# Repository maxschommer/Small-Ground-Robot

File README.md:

# Small-Ground-Robot
A small, autonomous ground vehicle.

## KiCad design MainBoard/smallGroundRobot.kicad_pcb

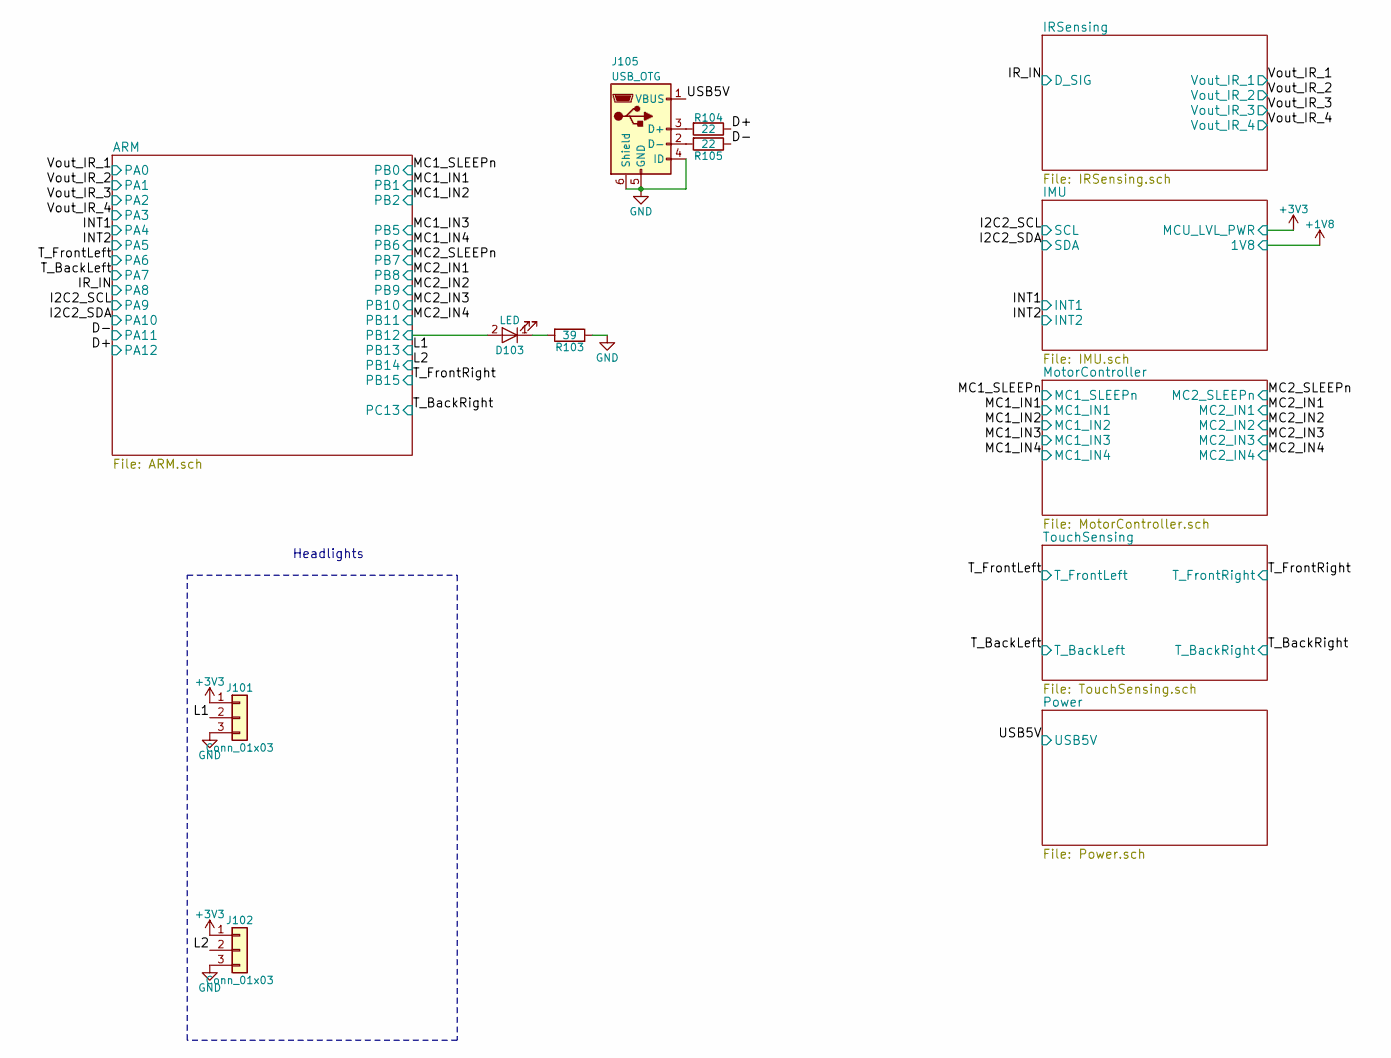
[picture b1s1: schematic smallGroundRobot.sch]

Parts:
D103: LED; LED_0805
J101, J102: Conn_01x03; Pin_Header_Angled_1x03_Pitch2.54mm
J105: USB_OTG; USB_Micro-B
R103: 39; R_0402
R104, R105: 22; R_0402

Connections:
+3V3: J101.1, J102.1; also elsewhere on the board
/ARM/PB12: D103.2 (A); also elsewhere on the board
/D+: R104.1; also elsewhere on the board
/D-: R105.1; also elsewhere on the board
/L1: J101.2; also elsewhere on the board
/L2: J102.2; also elsewhere on the board
/USB5V: J105.1 (VBUS); also elsewhere on the board
GND: J101.3, J102.3, J105.4 (ID), J105.5 (GND), J105.6 (Shield), R103.1; also elsewhere on the board
unnamed: D103.1 (K), R103.2
unnamed: J105.2 (D-), R105.2
unnamed: J105.3 (D+), R104.2

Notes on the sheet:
Headlights

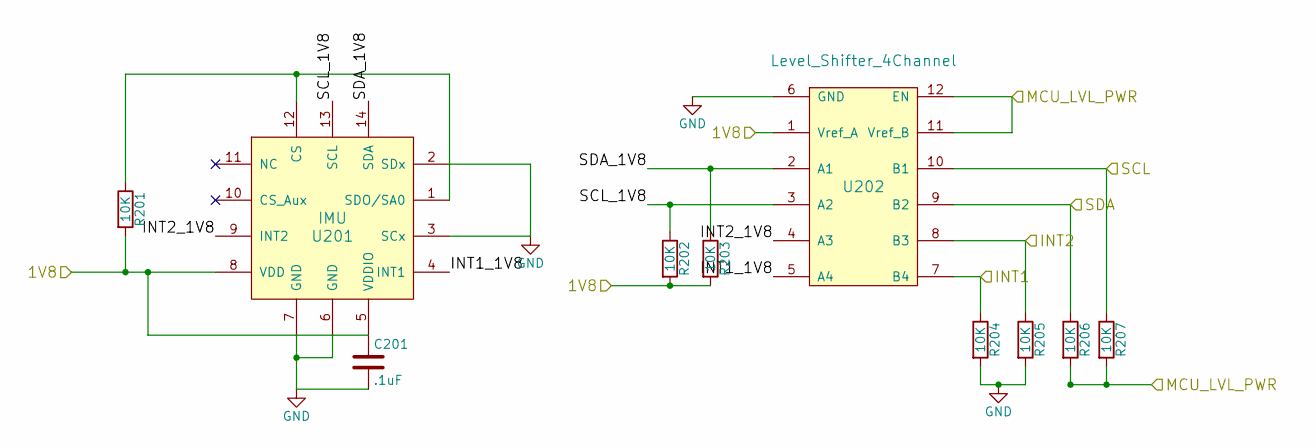
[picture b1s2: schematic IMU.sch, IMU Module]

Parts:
C201: .1uF; C_0402
R201, R202, R203, R204, R205, R206, R207: 10K; R_0402
U201: IMU; Bosch_LGA-14_3x2.5mm_Pitch0.5mm
U202: Level_Shifter_4Channel; R-PUQFN-N12

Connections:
+1V8: C201.1, R201.2, R202.2, R203.2, U201.5 (VDDIO), U201.8 (VDD), U202.1 (Vref_A); also elsewhere on the board
+3V3: R206.2, R207.2, U202.11 (Vref_B), U202.12 (EN); also elsewhere on the board
/I2C2_SCL: R207.1, U202.10 (B1); also elsewhere on the board
/I2C2_SDA: R206.1, U202.9 (B2); also elsewhere on the board
/IMU/INT1_1V8: U201.4 (INT1), U202.5 (A4)
/IMU/INT2_1V8: U201.9 (INT2), U202.4 (A3)
/IMU/SCL_1V8: R202.1, U201.13 (SCL), U202.3 (A2)
/IMU/SDA_1V8: R203.1, U201.14 (SDA), U202.2 (A1)
/INT1: R204.1, U202.7 (B4); also elsewhere on the board
/INT2: R205.1, U202.8 (B3); also elsewhere on the board
GND: C201.2, R204.2, R205.2, U201.2 (SDx), U201.3 (SCx), U201.6 (GND), U201.7 (GND), U202.6 (GND); also elsewhere on the board
unnamed: R201.1, U201.1 (SDO/SA0), U201.12 (CS)

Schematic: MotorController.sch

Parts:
C301, C303: .1uF; C_0402
M301, M302, M303, M304: Motor_DC; Motor_6V_96RPM
R301, R302, R303, R304, R305, R306: 10k; R_0402
U301, U302: A3916; QFN-16-1EP_3x3mm_Pitch0.5mm_ThermalVias

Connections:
+3V3: R301.2, R304.2; also elsewhere on the board
/MC1_IN1: U301.3 (IN1); also elsewhere on the board
/MC1_IN2: U301.4 (IN2); also elsewhere on the board
/MC1_IN3: U301.5 (IN3); also elsewhere on the board
/MC1_IN4: U301.6 (IN4); also elsewhere on the board
/MC1_SLEEPn: U301.2 (SLEEPn); also elsewhere on the board
/MC2_IN1: U302.3 (IN1); also elsewhere on the board
/MC2_IN2: U302.4 (IN2); also elsewhere on the board
/MC2_IN3: U302.5 (IN3); also elsewhere on the board
/MC2_IN4: U302.6 (IN4); also elsewhere on the board
/MC2_SLEEPn: U302.2 (SLEEPn); also elsewhere on the board
GND: R302.1, R303.1, R305.1, R306.1, U301.1 (GND), U302.1 (GND); also elsewhere on the board
unnamed: C301.1, U301.15 (VCP)
unnamed: C303.1, U302.15 (VCP)
unnamed: M301.1 (+), U301.14 (OUT1A)
unnamed: M301.2 (-), U301.12 (OUT1B)
unnamed: M302.1 (+), U301.8 (OUT2A)
unnamed: M302.2 (-), U301.10 (OUT2B)
unnamed: M303.1 (+), U302.14 (OUT1A)
unnamed: M303.2 (-), U302.12 (OUT1B)
unnamed: M304.1 (+), U302.8 (OUT2A)
unnamed: M304.2 (-), U302.10 (OUT2B)
unnamed: R301.1, U301.7 (FAULTn)
unnamed: R302.2, U301.9 (SENSE2)
unnamed: R303.2, U301.13 (SENSE1)
unnamed: R304.1, U302.7 (FAULTn)
unnamed: R305.2, U302.9 (SENSE2)
unnamed: R306.2, U302.13 (SENSE1)

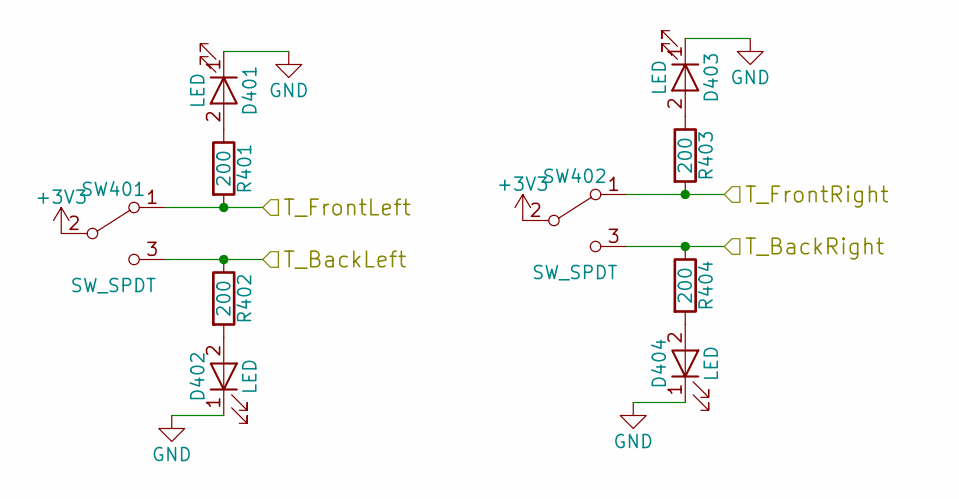
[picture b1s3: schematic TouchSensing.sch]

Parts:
D401, D402, D403, D404: LED; LED_0805
R401, R402, R403, R404: 200; R_0402
SW401, SW402: SW_SPDT; TouchSensor

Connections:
+3V3: SW401.2 (B), SW402.2 (B); also elsewhere on the board
/T_BackLeft: R402.1, SW401.3 (C); also elsewhere on the board
/T_BackRight: R404.1, SW402.3 (C); also elsewhere on the board
/T_FrontLeft: R401.2, SW401.1 (A); also elsewhere on the board
/T_FrontRight: R403.2, SW402.1 (A); also elsewhere on the board
GND: D401.1 (K), D402.1 (K), D403.1 (K), D404.1 (K); also elsewhere on the board
unnamed: D401.2 (A), R401.1
unnamed: D402.2 (A), R402.2
unnamed: D403.2 (A), R403.1
unnamed: D404.2 (A), R404.2

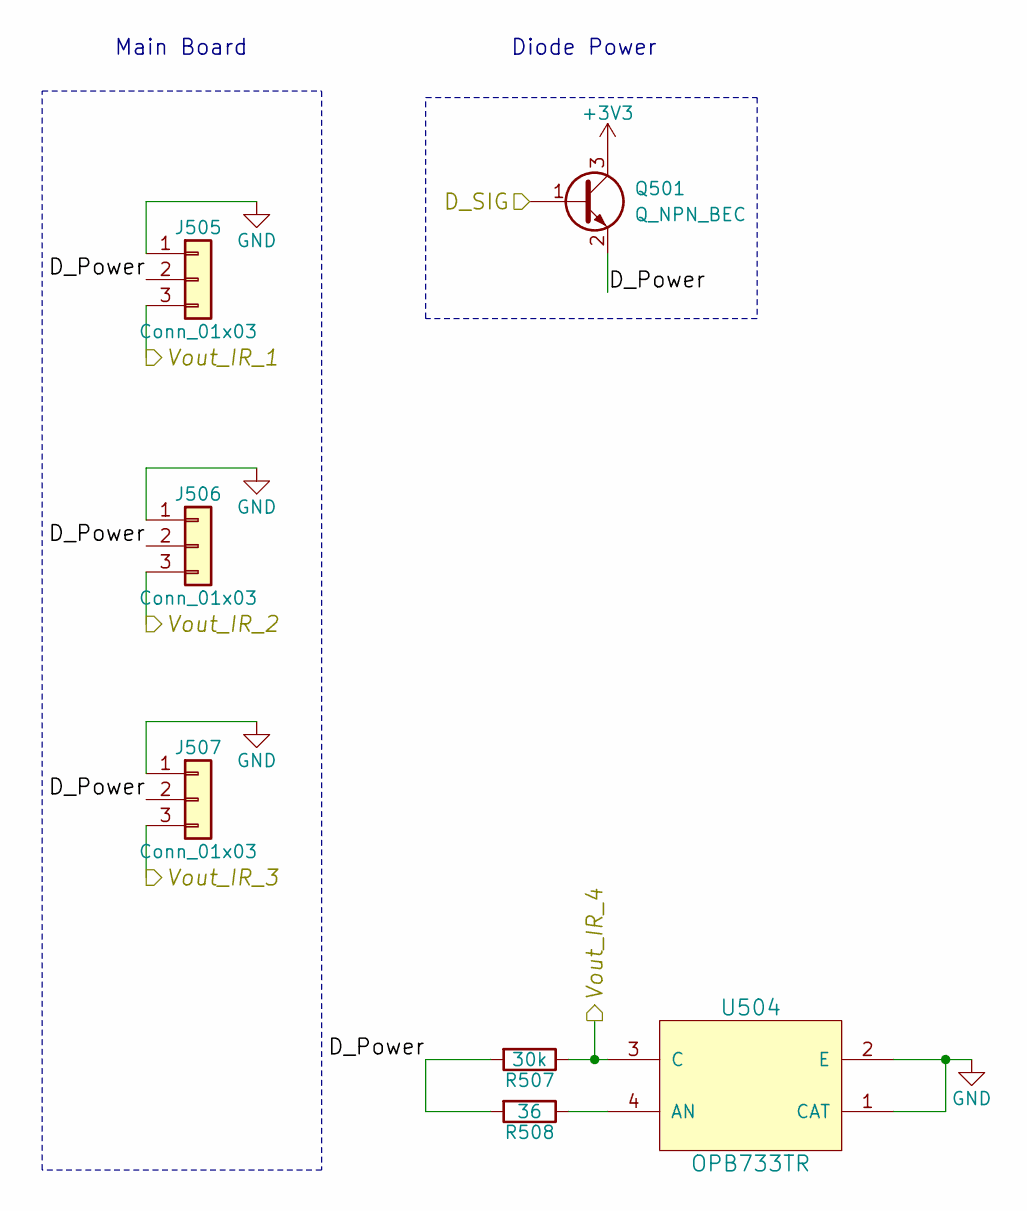
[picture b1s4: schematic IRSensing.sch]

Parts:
J505, J506, J507: Conn_01x03; Pin_Header_Angled_1x03_Pitch2.54mm
Q501: Q_NPN_BEC; SOT-23
R507: 30k; R_0402
R508: 36; R_0402
U504: OPB733TR

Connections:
+3V3: Q501.3 (C); also elsewhere on the board
/IRSensing/D_Power: J505.2, J506.2, J507.2, Q501.2 (E), R507.2, R508.2
/IR_IN: Q501.1 (B); also elsewhere on the board
/Vout_IR_1: J505.3; also elsewhere on the board
/Vout_IR_2: J506.3; also elsewhere on the board
/Vout_IR_3: J507.3; also elsewhere on the board
/Vout_IR_4: R507.1, U504.3 (C); also elsewhere on the board
GND: J505.1, J506.1, J507.1, U504.1 (CAT), U504.2 (E); also elsewhere on the board
unnamed: R508.1, U504.4 (AN)

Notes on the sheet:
Main Board
Diode Power

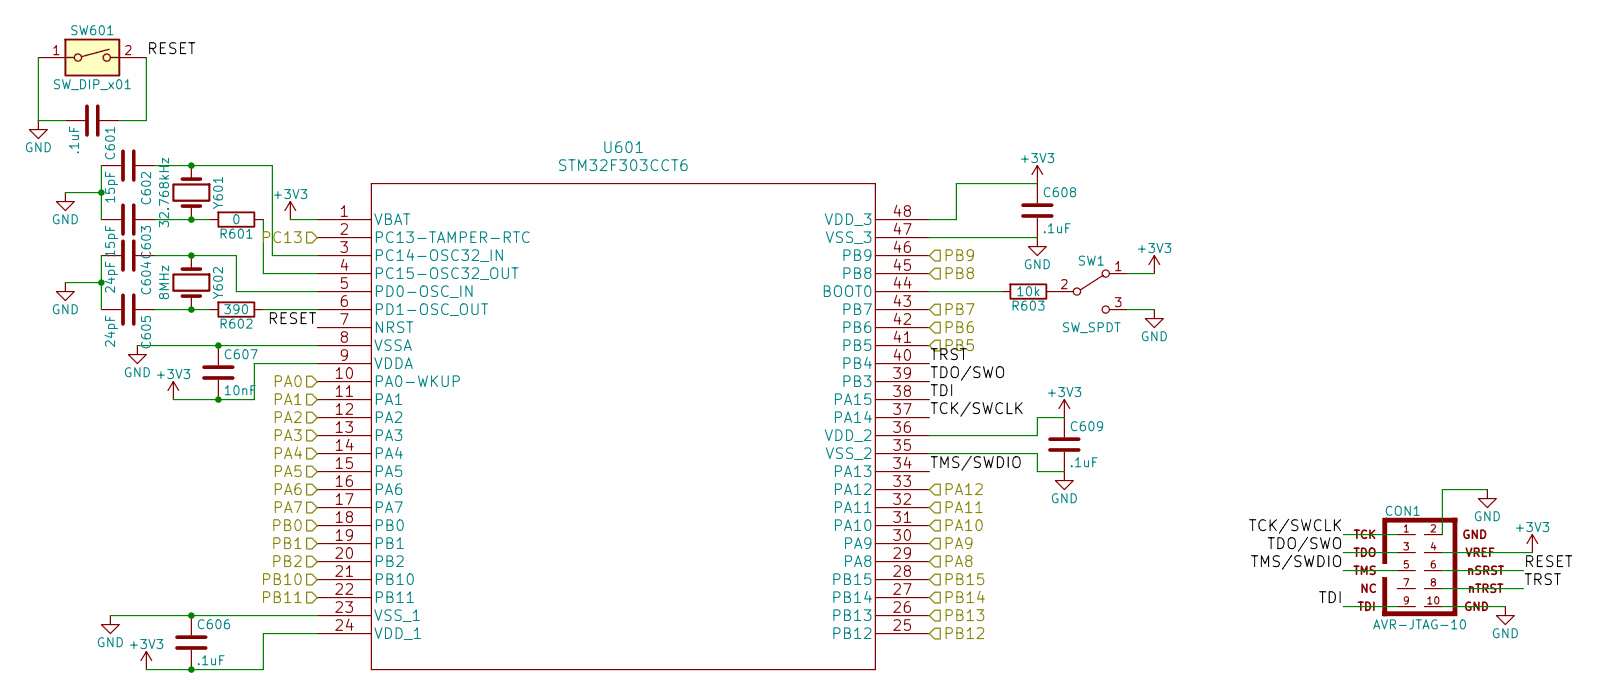
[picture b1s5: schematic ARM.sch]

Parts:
C601, C606, C608, C609: .1uF; C_0402
C602, C603: 15pF; C_0402
C604, C605: 24pF; C_0402
C607: 10nF; C_0402
CON1: AVR-JTAG-10; Pin_Header_Straight_2x05_Pitch2.54mm
R601: 0; R_0402
R602: 390; R_0402
R603: 10k; R_0402
SW1: SW_SPDT; SW_SPDT_PCM12
SW601: SW_DIP_x01; KMT071_NGJ_LHS
U601: STM32F303CCT6
Y601: 32.768kHz; ECS-.327-12.5-34B-TR
Y602: 8MHz; ABM3-8.000MHZ-D2Y-T

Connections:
+3V3: C606.2, C607.2, C608.1, C609.1, CON1.4, SW1.1 (A), U601.1 (VBAT), U601.9 (VDDA), U601.24 (VDD_1), U601.36 (VDD_2), U601.48 (VDD_3); also elsewhere on the board
/ARM/PB12: U601.25 (PB12); also elsewhere on the board
/ARM/RESET: C601.1, CON1.6, SW601.2, U601.7 (NRST)
/ARM/TCK/SWCLK: CON1.1, U601.37 (PA14)
/ARM/TDI: CON1.9, U601.38 (PA15)
/ARM/TDO/SWO: CON1.3, U601.39 (PB3)
/ARM/TMS/SWDIO: CON1.5, U601.34 (PA13)
/ARM/TRST: CON1.8, U601.40 (PB4)
/D+: U601.33 (PA12); also elsewhere on the board
/D-: U601.32 (PA11); also elsewhere on the board
/I2C2_SCL: U601.30 (PA9); also elsewhere on the board
/I2C2_SDA: U601.31 (PA10); also elsewhere on the board
/INT1: U601.14 (PA4); also elsewhere on the board
/INT2: U601.15 (PA5); also elsewhere on the board
/IR_IN: U601.29 (PA8); also elsewhere on the board
/L1: U601.26 (PB13); also elsewhere on the board
/L2: U601.27 (PB14); also elsewhere on the board
/MC1_IN1: U601.19 (PB1); also elsewhere on the board
/MC1_IN2: U601.20 (PB2); also elsewhere on the board
/MC1_IN3: U601.41 (PB5); also elsewhere on the board
/MC1_IN4: U601.42 (PB6); also elsewhere on the board
/MC1_SLEEPn: U601.18 (PB0); also elsewhere on the board
/MC2_IN1: U601.45 (PB8); also elsewhere on the board
/MC2_IN2: U601.46 (PB9); also elsewhere on the board
/MC2_IN3: U601.21 (PB10); also elsewhere on the board
/MC2_IN4: U601.22 (PB11); also elsewhere on the board
/MC2_SLEEPn: U601.43 (PB7); also elsewhere on the board
/T_BackLeft: U601.17 (PA7); also elsewhere on the board
/T_BackRight: U601.2 (PC13-TAMPER-RTC); also elsewhere on the board
/T_FrontLeft: U601.16 (PA6); also elsewhere on the board
/T_FrontRight: U601.28 (PB15); also elsewhere on the board
/Vout_IR_1: U601.10 (PA0-WKUP); also elsewhere on the board
/Vout_IR_2: U601.11 (PA1); also elsewhere on the board
/Vout_IR_3: U601.12 (PA2); also elsewhere on the board
/Vout_IR_4: U601.13 (PA3); also elsewhere on the board
GND: C601.2, C602.2, C603.2, C604.2, C605.2, C606.1, C607.1, C608.2, C609.2, CON1.2, CON1.10, SW1.3 (C), SW601.1, U601.8 (VSSA), U601.23 (VSS_1), U601.35 (VSS_2), U601.47 (VSS_3); also elsewhere on the board
unnamed: C602.1, U601.3 (PC14-OSC32_IN), Y601.1
unnamed: C603.1, R601.2, Y601.2
unnamed: C604.1, U601.5 (PD0-OSC_IN), Y602.1
unnamed: C605.1, R602.2, Y602.2
unnamed: R601.1, U601.4 (PC15-OSC32_OUT)
unnamed: R602.1, U601.6 (PD1-OSC_OUT)
unnamed: R603.1, SW1.2 (B)
unnamed: R603.2, U601.44 (BOOT0)

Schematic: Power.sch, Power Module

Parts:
C1, C701, C702, C705, C707: 10uF; C_0603
C703, C704: 4.7uF; C_0603
C706: 1uF; C_0603
D1: R_LED_6V; LED_0805
D701, D703: R_LED_3V3; LED_0805
D702: R_LED_USB5V; LED_0805
D704: R_LED_PGOOD; LED_0805
D705: R_LED_CHG; LED_0805
J701: Screw_Terminal_01x02; TerminalBlock_Phoenix_MPT-2.54mm_2pol
L1: 4.7uH; L_0603
L701, L702: 2.2uH; L_0603
R1: 2.55k; R_0402
R2: 10k; R_0402
R3: 500; R_0402
R701: 200; R_0402
R702: 400; R_0402
R703: 0; R_0402
R704: 10K; R_0402
R705: 3.57K; R_0402
R706, R708: 1.5K; R_0402
R707: 2.94K; R_0402
R709: 4.32K; R_0402
R710: 56.2K; R_0402
U1: ST8R00WPUR; DFN-8-1EP_4x4mm_Pitch0.8mm
U701: TPS62237; TPS62237DRYR
U702: TPS62231; TPS62231DRYR
U703: BQ2423; QFN-16-1EP_3x3mm_Pitch0.5mm_ThermalVias

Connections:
+1V8: C704.1, L702.1, R703.1, U702.6 (FB); also elsewhere on the board
+3V3: C703.1, L701.1, R701.1, U1.6 (INH), U701.6 (FB); also elsewhere on the board
/Power/3V7: C1.1, C701.1, C702.1, C707.2, L1.2, R706.1, R708.1, U1.4 (IN), U701.3 (VIN), U701.5 (EN), U702.3 (VIN), U702.5 (EN), U703.5 (EN2), U703.10 (OUT), U703.11 (OUT)
/USB5V: C706.1, R702.1, U703.13 (IN); also elsewhere on the board
GND: C1.2, C701.2, C702.2, C703.2, C704.2, C705.2, C706.2, C707.1, D1.1 (K), D701.1 (K), D702.1 (K), D703.1 (K), J701.1, R2.2, R704.1, R705.2, R707.2, R709.2, R710.2, U1.2 (PGND), U1.3 (GND), U1.9 (EXPpad), U701.1 (MODE), U701.4 (GND), U702.1 (MODE), U702.4 (GND), U703.4 (~CE), U703.6 (EN1), U703.8 (VSS); also elsewhere on the board
unnamed: C705.1, J701.2, U703.2 (BAT), U703.3 (BAT)
unnamed: D1.2 (A), R3.2
unnamed: D701.2 (A), R701.2
unnamed: D702.2 (A), R702.2
unnamed: D703.2 (A), R703.2
unnamed: D704.1 (K), U703.7 (~PGOOD)
unnamed: D704.2 (A), R706.2
unnamed: D705.1 (K), U703.9 (~CHG)
unnamed: D705.2 (A), R708.2
unnamed: L1.1, U1.1 (LX)
unnamed: L701.2, U701.2 (SW)
unnamed: L702.2, U702.2 (SW)
unnamed: R1.2, R2.1, U1.5 (FB)
unnamed: R704.2, U703.1 (TS)
unnamed: R705.1, U703.15 (ITERM)
unnamed: R707.1, U703.12 (ILIM)
unnamed: R709.1, U703.16 (ISET)
unnamed: R710.1, U703.14 (TMR)

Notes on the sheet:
Battery Management
3V3 Regulator
Power Indicating LEDs
1V8 Regulator

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
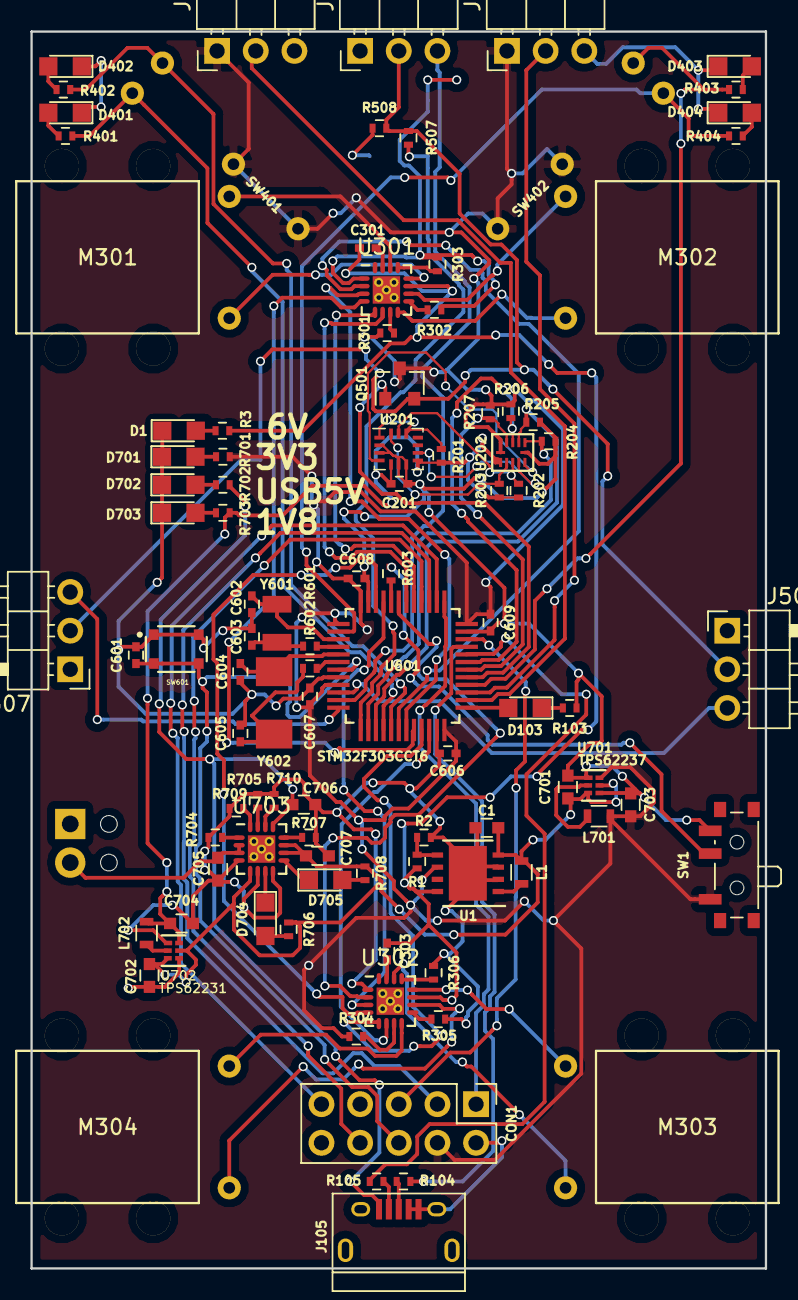
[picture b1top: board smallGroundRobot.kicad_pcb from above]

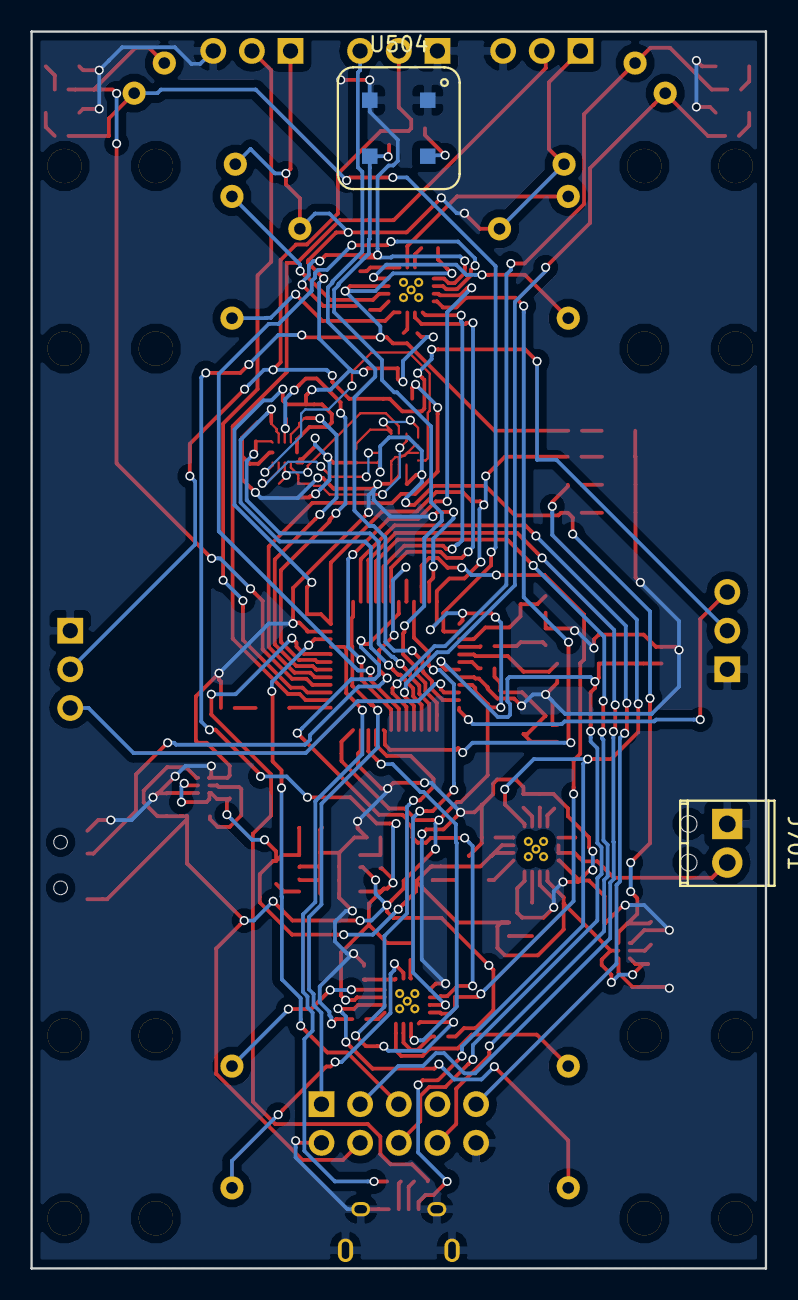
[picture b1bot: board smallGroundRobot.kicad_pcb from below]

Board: 2 copper layers, 48.3 x 81.3 mm, 101 parts (2 on the bottom side), 96 nets.

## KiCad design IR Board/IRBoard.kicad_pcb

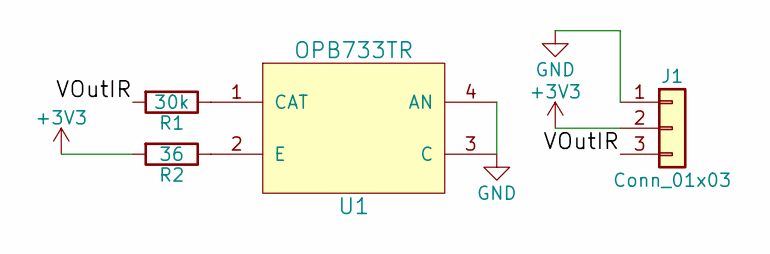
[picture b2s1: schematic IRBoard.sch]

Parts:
J1: Conn_01x03; Pin_Header_Angled_1x03_Pitch2.54mm
R1: 30k; R_0402
R2: 36; R_0402
U1: OPB733TR

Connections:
+3V3: J1.2, R2.2
/VOutIR: J1.3, R1.2
GND: J1.1, U1.3 (C), U1.4 (AN)
unnamed: R1.1, U1.1 (CAT)
unnamed: R2.1, U1.2 (E)

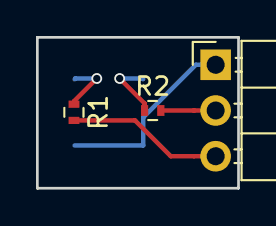
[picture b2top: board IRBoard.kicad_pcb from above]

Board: 2 copper layers, 11.2 x 8.4 mm, 4 parts (1 on the bottom side), 5 nets.

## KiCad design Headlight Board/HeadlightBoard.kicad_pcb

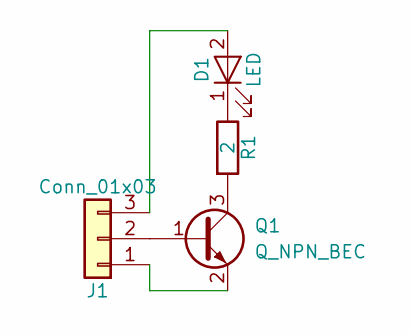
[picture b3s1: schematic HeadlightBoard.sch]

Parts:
D1: LED; LED_1206
J1: Conn_01x03; Pin_Header_Angled_1x03_Pitch2.54mm
Q1: Q_NPN_BEC; TSOT-23
R1: 2; R_0402

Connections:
unnamed: D1.1 (K), R1.1
unnamed: D1.2 (A), J1.3
unnamed: J1.1, Q1.2 (E)
unnamed: J1.2, Q1.1 (B)
unnamed: Q1.3 (C), R1.2

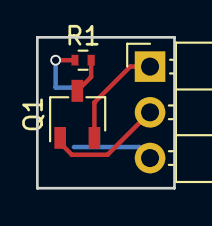
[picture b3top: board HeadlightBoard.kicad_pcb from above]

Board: 2 copper layers, 7.6 x 8.4 mm, 4 parts (1 on the bottom side), 5 nets.

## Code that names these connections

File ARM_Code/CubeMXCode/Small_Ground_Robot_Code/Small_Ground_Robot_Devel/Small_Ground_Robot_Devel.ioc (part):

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Mcu.Name=STM32F303C(B-C)Tx
Mcu.Package=LQFP48
Mcu.UserName=STM32F303CCTx
PA0.Signal=GPIO_Output
PA1.Signal=GPIO_Output
PA10.Signal=GPIO_Output
PA11.Signal=GPIO_Output
PA12.Signal=GPIO_Output
PA13.Mode=Serial_Wire
PA13.Signal=SYS_JTMS-SWDIO
PA14.Mode=Serial_Wire
PA14.Signal=SYS_JTCK-SWCLK
PA15.Signal=GPIO_Output
PA2.Signal=GPIO_Output
PA3.Signal=GPIO_Output
PA4.Signal=GPIO_Output
PA5.Signal=GPIO_Output
PA6.Signal=GPIO_Output
PA7.Signal=GPIO_Output
PA8.Signal=GPIO_Output
PA9.Signal=GPIO_Output
PB0.Signal=GPIO_Output
PB1.Signal=GPIO_Output
PB10.Signal=GPIO_Output
PB11.Signal=GPIO_Output
PB12.Signal=GPIO_Output
PB13.Signal=GPIO_Output
PB14.Signal=GPIO_Output
PB15.Signal=GPIO_Output
PB2.Signal=GPIO_Output
PB3.Signal=GPIO_Output
PB4.Signal=GPIO_Output
PB5.Signal=GPIO_Output
PB6.Signal=GPIO_Output
PB7.Signal=GPIO_Output
PB8.Signal=GPIO_Output
PB9.Signal=GPIO_Output
PC13.Signal=GPIO_Output
PC14-OSC32_IN.Signal=GPIO_Output
PC15-OSC32_OUT.Signal=GPIO_Output
PF0-OSC_IN.Signal=GPIO_Output
PF1-OSC_OUT.Signal=GPIO_Output
RCC.HSEPLLFreq_Value=8000000
RCC.HSE_VALUE=8000000
RCC.SYSCLKFreq_VALUE=8000000
board=Small_Ground_Robot_Devel

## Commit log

2018-02-10 Initialized kicad files
2018-02-24 Added touch sensor design
2018-03-04 Added IR Sensor foorprint + PCB
2018-03-05 Adding IR sensor circuit
2018-03-09 Built arm processor
2018-03-11 Added power, touch, and motor controller
2018-03-13 Pushing deleted stuff
2018-03-13 Adding IR Sensor
2018-03-13 Added IMU module
2018-04-02 Finished Schematic
2018-04-09 Started associating footprints
2018-04-29 Finished board designs
2018-05-07 Modified schematic for correct footprint
2018-05-16 Modified design to have working 6V

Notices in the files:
parts and their libraries:
Copyright 2016 Accelerated Designs. All rights reserved.
